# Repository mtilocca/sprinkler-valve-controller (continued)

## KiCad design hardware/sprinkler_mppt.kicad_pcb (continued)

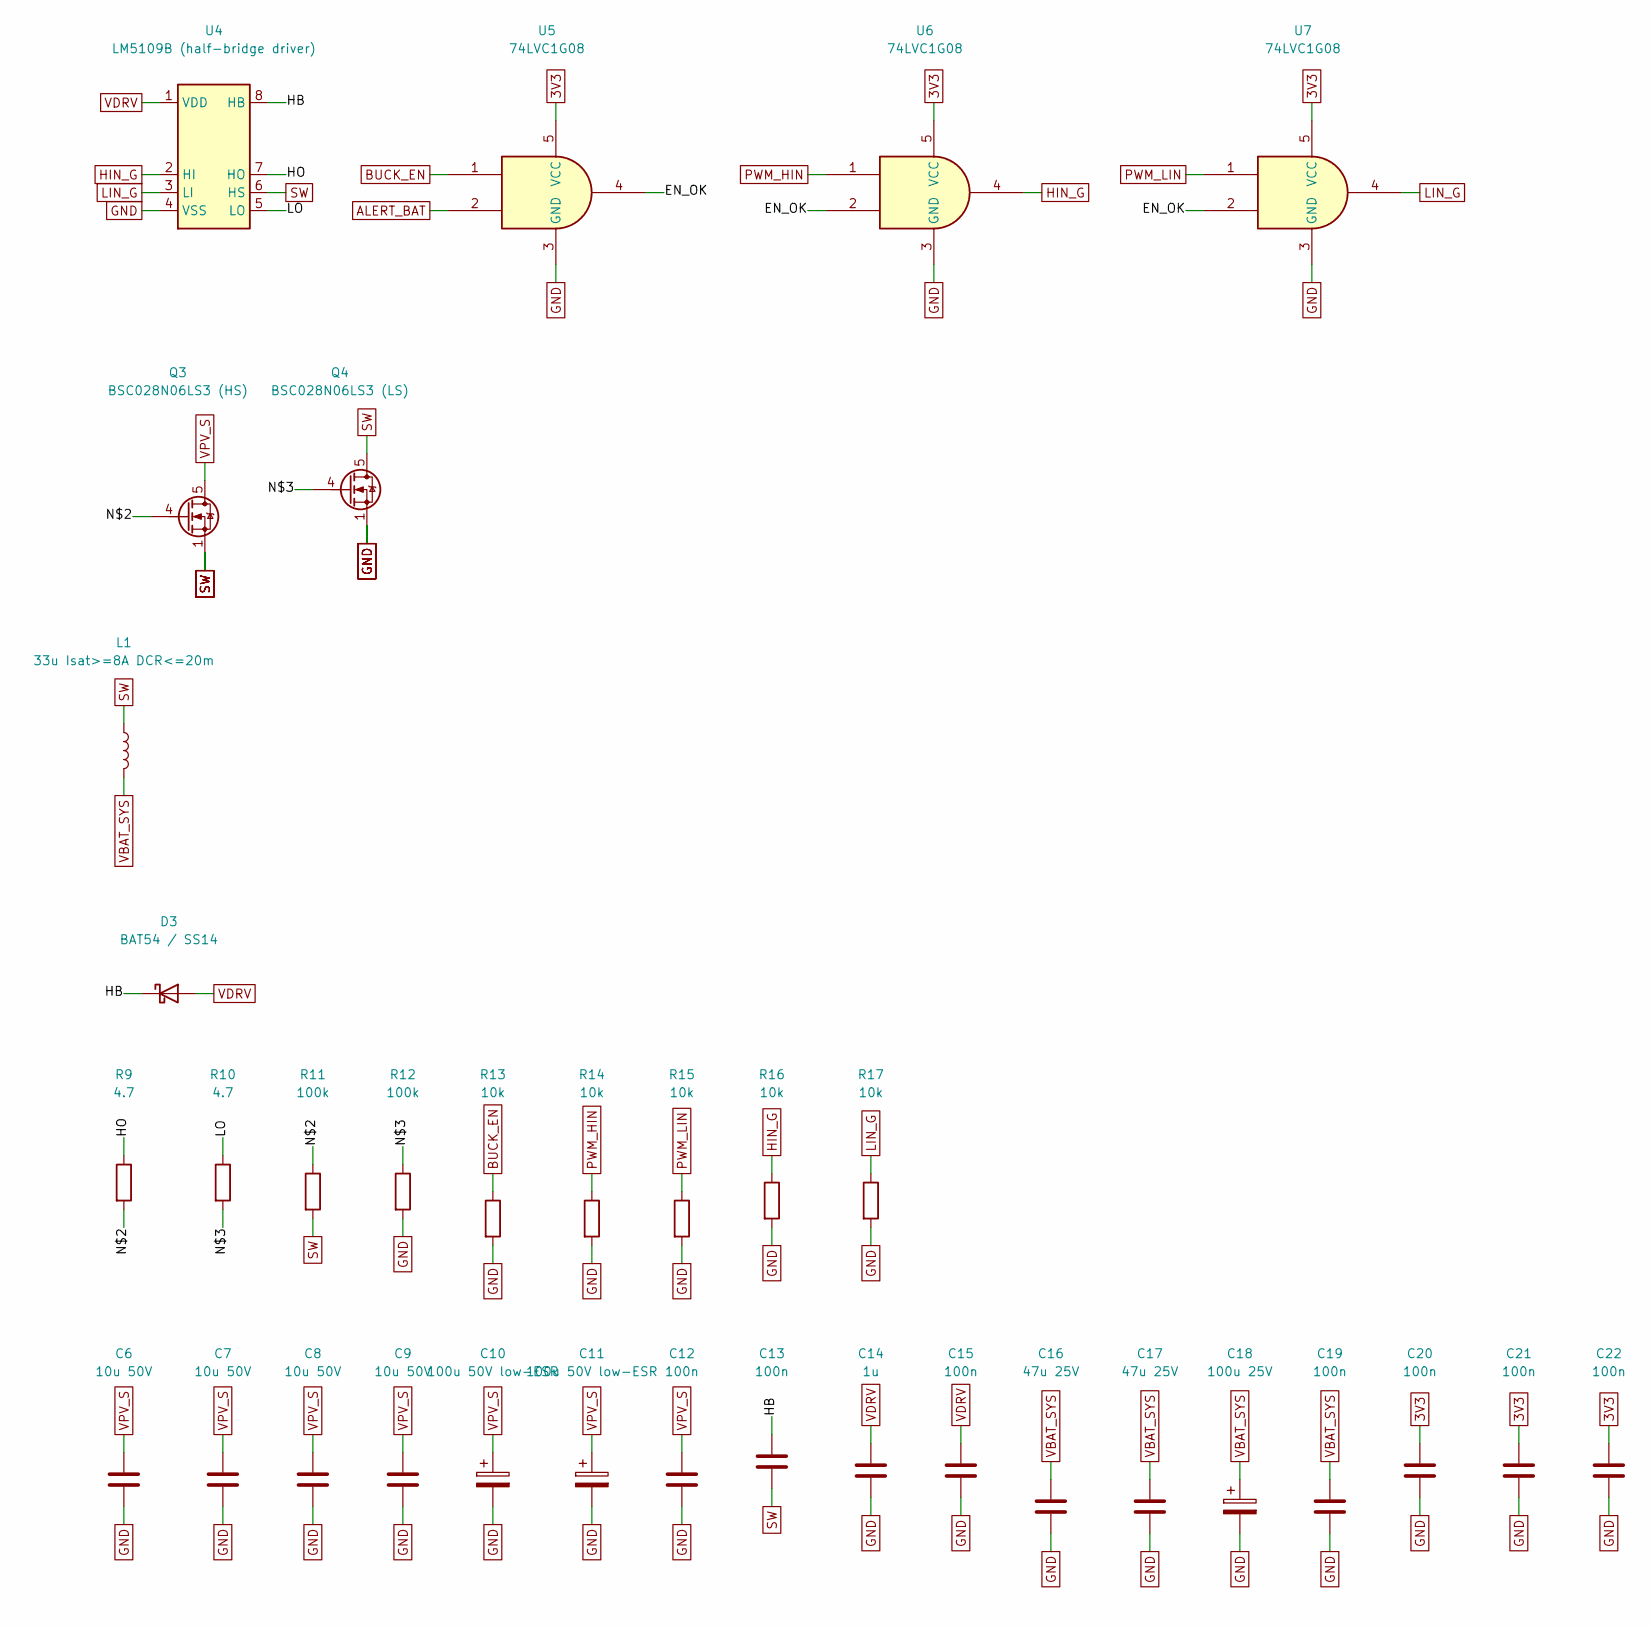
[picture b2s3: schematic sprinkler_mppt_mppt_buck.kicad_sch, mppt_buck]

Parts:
C6, C7, C8, C9: 10u 50V; C_1210_3225Metric
C10, C11: 100u 50V low-ESR; CP_Elec_8x10
C12, C13, C15, C19, C20, C21, C22: 100n; C_0603_1608Metric
C14: 1u; C_0603_1608Metric
C16, C17: 47u 25V; C_1210_3225Metric
C18: 100u 25V; CP_Elec_8x10
D3: BAT54 / SS14; D_SOD-123
L1: 33u Isat>=8A DCR<=20m; L_Bourns_SRP1245A
Q3: BSC028N06LS3 (HS); TDSON-8-1
Q4: BSC028N06LS3 (LS); TDSON-8-1
R9, R10: 4.7; R_0603_1608Metric
R11, R12: 100k; R_0603_1608Metric
R13, R14, R15, R16, R17: 10k; R_0603_1608Metric
U4: LM5109B (half-bridge driver); SOIC-8_3.9x4.9mm_P1.27mm
U5, U6, U7: 74LVC1G08; SOT-353_SC-70-5

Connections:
3V3: C20.1, C21.1, C22.1, U5.5 (VCC), U6.5 (VCC), U7.5 (VCC); also elsewhere on the board
/mppt_buck/EN_OK: U5.4, U6.2, U7.2
/mppt_buck/HB: C13.1, D3.1 (K), U4.8 (HB)
/mppt_buck/HO: R9.1, U4.7 (HO)
/mppt_buck/LO: R10.1, U4.5 (LO)
/mppt_buck/N$2: Q3.4 (G), R9.2, R11.1
/mppt_buck/N$3: Q4.4 (G), R10.2, R12.1
ALERT_BAT: U5.2; also elsewhere on the board
BUCK_EN: R13.1, U5.1; also elsewhere on the board
GND: C6.2, C7.2, C8.2, C9.2, C10.2, C11.2, C12.2, C14.2, C15.2, C16.2, C17.2, C18.2, C19.2, C20.2, C21.2, C22.2, Q4.1 (S), Q4.2 (S), Q4.3 (S), R12.2, R13.2, R14.2, R15.2, R16.2, R17.2, U4.4 (VSS), U5.3 (GND), U6.3 (GND), U7.3 (GND); also elsewhere on the board
HIN_G: R16.1, U4.2 (HI), U6.4; also elsewhere on the board
LIN_G: R17.1, U4.3 (LI), U7.4; also elsewhere on the board
PWM_HIN: R14.1, U6.1; also elsewhere on the board
PWM_LIN: R15.1, U7.1; also elsewhere on the board
SW: C13.2, L1.1, Q3.1 (S), Q3.2 (S), Q3.3 (S), Q4.5 (D), R11.2, U4.6 (HS); also elsewhere on the board
VBAT_SYS: C16.1, C17.1, C18.1, C19.1, L1.2; also elsewhere on the board
VDRV: C14.1, C15.1, D3.2 (A), U4.1 (VDD); also elsewhere on the board
VPV_S: C6.1, C7.1, C8.1, C9.1, C10.1, C11.1, C12.1, Q3.5 (D); also elsewhere on the board

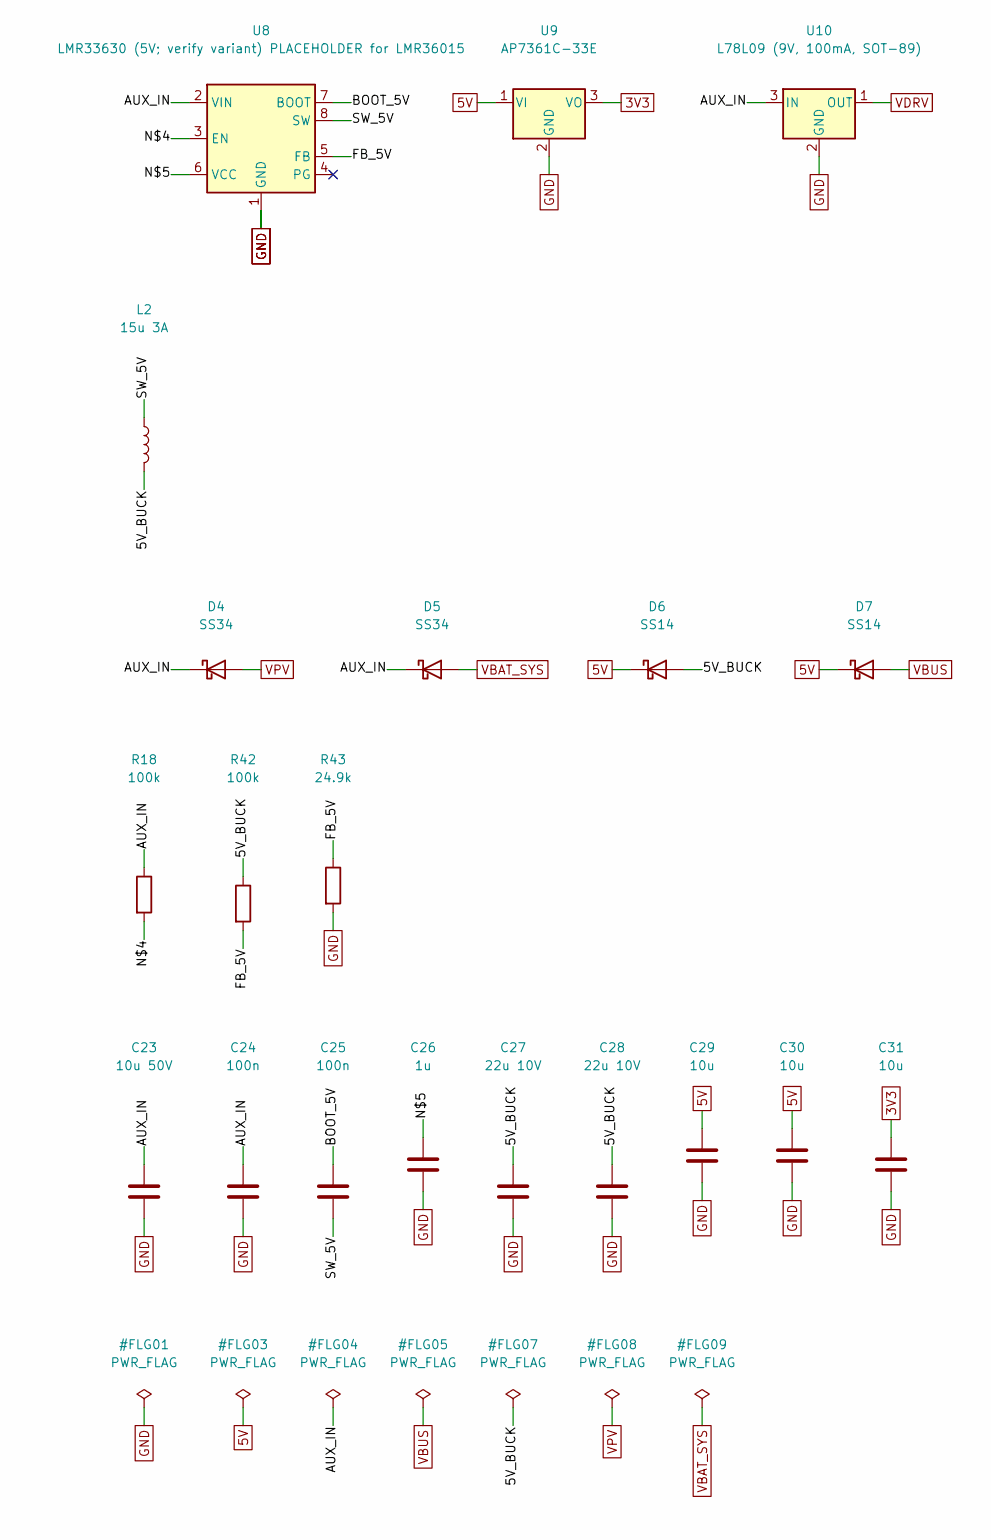
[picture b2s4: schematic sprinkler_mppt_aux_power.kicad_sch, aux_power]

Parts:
C23: 10u 50V; C_1210_3225Metric
C24, C25: 100n; C_0603_1608Metric
C26: 1u; C_0603_1608Metric
C27, C28: 22u 10V; C_1206_3216Metric
C29, C30, C31: 10u; C_1206_3216Metric
D4, D5: SS34; D_SMA
D6, D7: SS14; D_SMA
L2: 15u 3A; L_Bourns_SRN6045TA
R18: 100k; R_0603_1608Metric
R42: 100k; R_0402_1005Metric
R43: 24.9k; R_0402_1005Metric
U8: LMR33630 (5V; verify variant) PLACEHOLDER for LMR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; Texas_HSOP-8-1EP_3.9x4.9mm_P1.27mm_ThermalVias
U9: AP7361C-33E; SOT-223-3_TabPin2
U10: L78L09 (9V, 100mA, SOT-89); SOT-89-3

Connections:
3V3: C31.1, U9.3 (VO); also elsewhere on the board
5V: C29.1, C30.1, D6.1 (K), D7.1 (K), U9.1 (VI); also elsewhere on the board
/aux_power/5V_BUCK: C27.1, C28.1, D6.2 (A), L2.2, R42.1
/aux_power/AUX_IN: C23.1, C24.1, D4.1 (K), D5.1 (K), R18.1, U8.2 (VIN), U10.3 (IN)
/aux_power/BOOT_5V: C25.1, U8.7 (BOOT)
/aux_power/FB_5V: R42.2, R43.1, U8.5 (FB)
/aux_power/N$4: R18.2, U8.3 (EN)
/aux_power/N$5: C26.1, U8.6 (VCC)
/aux_power/SW_5V: C25.2, L2.1, U8.8 (SW)
GND: C23.2, C24.2, C26.2, C27.2, C28.2, C29.2, C30.2, C31.2, R43.2, U8.1 (GND), U8.9 (GND), U9.2 (GND), U10.2 (GND); also elsewhere on the board
VBAT_SYS: D5.2 (A); also elsewhere on the board
VBUS: D7.2 (A); also elsewhere on the board
VDRV: U10.1 (OUT); also elsewhere on the board
VPV: D4.2 (A); also elsewhere on the board

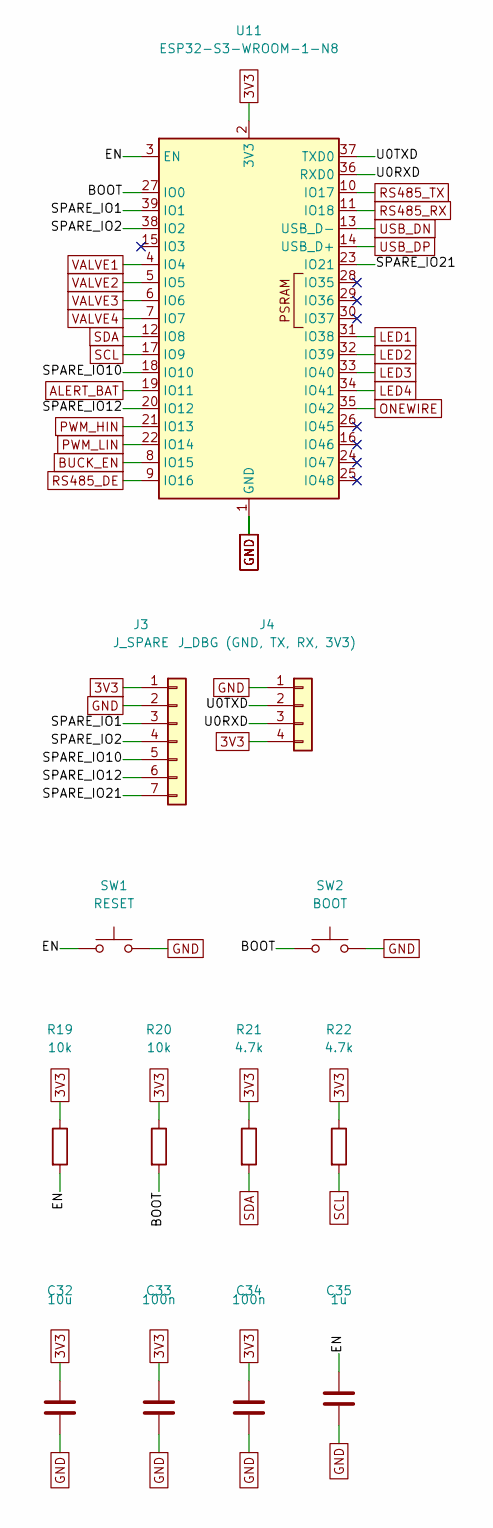
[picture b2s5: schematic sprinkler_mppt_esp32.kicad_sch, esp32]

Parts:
C32: 10u; C_1206_3216Metric
C33, C34: 100n; C_0603_1608Metric
C35: 1u; C_0603_1608Metric
J3: J_SPARE; PinHeader_1x07_P2.54mm_Vertical
J4: J_DBG (GND, TX, RX, 3V3); PinHeader_1x04_P2.54mm_Vertical
R19, R20: 10k; R_0603_1608Metric
R21, R22: 4.7k; R_0603_1608Metric
SW1: RESET; SW_SPST_PTS645Sx43SMTR92
SW2: BOOT; SW_SPST_PTS645Sx43SMTR92
U11: ESP32-S3-WROOM-1-N8; ESP32-S3-WROOM-1

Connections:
3V3: C32.1, C33.1, C34.1, J3.1, J4.4, R19.1, R20.1, R21.1, R22.1, U11.2 (3V3); also elsewhere on the board
/esp32/BOOT: R20.2, SW2.1, U11.27 (IO0)
/esp32/EN: C35.1, R19.2, SW1.1, U11.3 (EN)
/esp32/SPARE_IO1: J3.3, U11.39 (IO1)
/esp32/SPARE_IO2: J3.4, U11.38 (IO2)
/esp32/SPARE_IO10: J3.5, U11.18 (IO10)
/esp32/SPARE_IO12: J3.6, U11.20 (IO12)
/esp32/SPARE_IO21: J3.7, U11.23 (IO21)
/esp32/U0RXD: J4.3, U11.36 (RXD0)
/esp32/U0TXD: J4.2, U11.37 (TXD0)
ALERT_BAT: U11.19 (IO11); also elsewhere on the board
BUCK_EN: U11.8 (IO15); also elsewhere on the board
GND: C32.2, C33.2, C34.2, C35.2, J3.2, J4.1, SW1.2, SW2.2, U11.1 (GND), U11.40 (GND), U11.41 (GND); also elsewhere on the board
LED1: U11.31 (IO38); also elsewhere on the board
LED2: U11.32 (IO39); also elsewhere on the board
LED3: U11.33 (IO40); also elsewhere on the board
LED4: U11.34 (IO41); also elsewhere on the board
ONEWIRE: U11.35 (IO42); also elsewhere on the board
PWM_HIN: U11.21 (IO13); also elsewhere on the board
PWM_LIN: U11.22 (IO14); also elsewhere on the board
RS485_DE: U11.9 (IO16); also elsewhere on the board
RS485_RX: U11.11 (IO18); also elsewhere on the board
RS485_TX: U11.10 (IO17); also elsewhere on the board
SCL: R22.2, U11.17 (IO9); also elsewhere on the board
SDA: R21.2, U11.12 (IO8); also elsewhere on the board
USB_DN: U11.13 (USB_D-); also elsewhere on the board
USB_DP: U11.14 (USB_D+); also elsewhere on the board
VALVE1: U11.4 (IO4); also elsewhere on the board
VALVE2: U11.5 (IO5); also elsewhere on the board
VALVE3: U11.6 (IO6); also elsewhere on the board
VALVE4: U11.7 (IO7); also elsewhere on the board

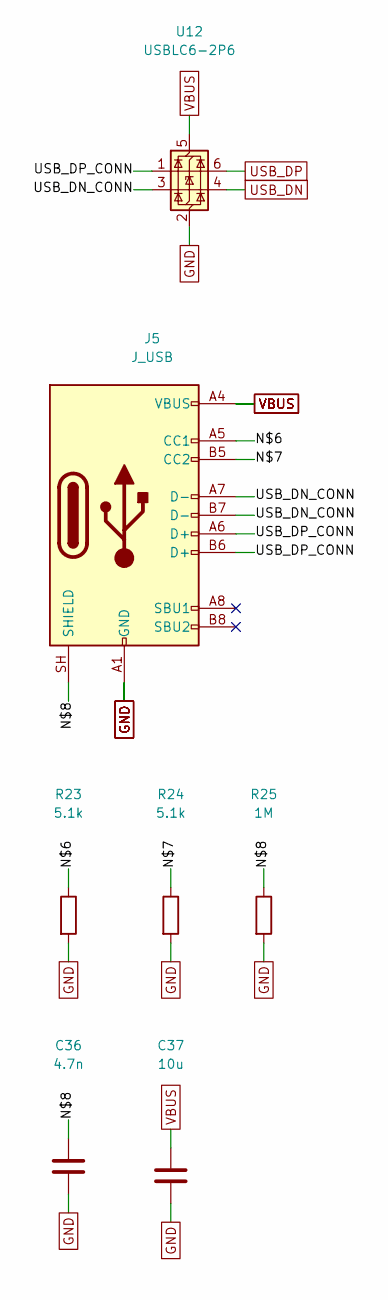
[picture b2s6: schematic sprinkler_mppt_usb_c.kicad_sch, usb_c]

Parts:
C36: 4.7n; C_0603_1608Metric
C37: 10u; C_1206_3216Metric
J5: J_USB; USB_C_Receptacle_HRO_TYPE-C-31-M-12
R23, R24: 5.1k; R_0603_1608Metric
R25: 1M; R_0603_1608Metric
U12: USBLC6-2P6; SOT-666

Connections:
/usb_c/N$6: J5.A5 (CC1), R23.1
/usb_c/N$7: J5.B5 (CC2), R24.1
/usb_c/N$8: C36.1, J5.SH (SHIELD), R25.1
/usb_c/USB_DN_CONN: J5.A7 (D-), J5.B7 (D-), U12.3 (I/O2)
/usb_c/USB_DP_CONN: J5.A6 (D+), J5.B6 (D+), U12.1 (I/O1)
GND: C36.2, C37.2, J5.A1 (GND), J5.A12 (GND), J5.B1 (GND), J5.B12 (GND), R23.2, R24.2, R25.2, U12.2 (GND); also elsewhere on the board
USB_DN: U12.4 (I/O2); also elsewhere on the board
USB_DP: U12.6 (I/O1); also elsewhere on the board
VBUS: C37.1, J5.A4 (VBUS), J5.A9 (VBUS), J5.B4 (VBUS), J5.B9 (VBUS), U12.5 (VBUS); also elsewhere on the board

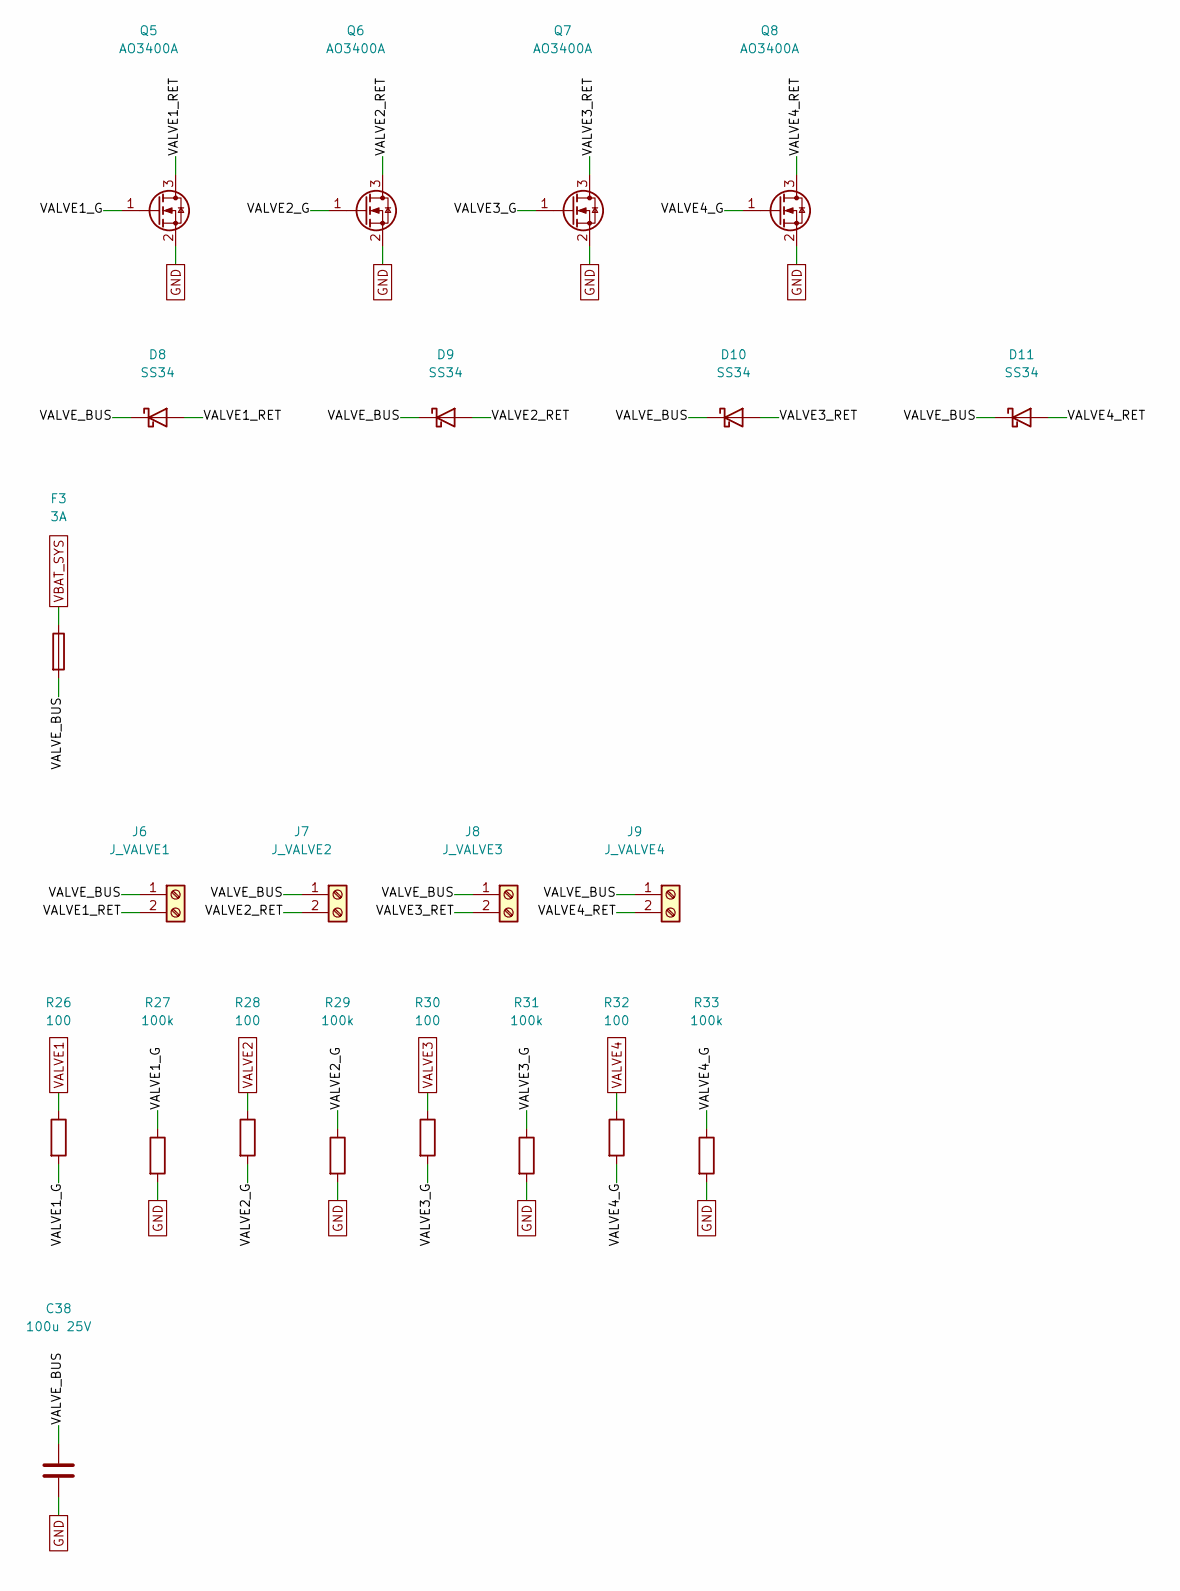
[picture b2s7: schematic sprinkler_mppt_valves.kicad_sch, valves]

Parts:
C38: 100u 25V; CP_Elec_8x10
D8, D9, D10, D11: SS34; D_SMA
F3: 3A; Fuse_1812_4532Metric
J6: J_VALVE1; TerminalBlock_Phoenix_MKDS-1,5-2-5.08_1x02_P5.08mm_Horizont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
J7: J_VALVE2; TerminalBlock_Phoenix_MKDS-1,5-2-5.08_1x02_P5.08mm_Horizont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
J8: J_VALVE3; TerminalBlock_Phoenix_MKDS-1,5-2-5.08_1x02_P5.08mm_Horizont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
J9: J_VALVE4; TerminalBlock_Phoenix_MKDS-1,5-2-5.08_1x02_P5.08mm_Horizont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
Q5, Q6, Q7, Q8: AO3400A; SOT-23
R26, R28, R30, R32: 100; R_0603_1608Metric
R27, R29, R31, R33: 100k; R_0603_1608Metric

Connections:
/valves/VALVE1_G: Q5.1 (G), R26.2, R27.1
/valves/VALVE1_RET: D8.2 (A), J6.2, Q5.3 (D)
/valves/VALVE2_G: Q6.1 (G), R28.2, R29.1
/valves/VALVE2_RET: D9.2 (A), J7.2, Q6.3 (D)
/valves/VALVE3_G: Q7.1 (G), R30.2, R31.1
/valves/VALVE3_RET: D10.2 (A), J8.2, Q7.3 (D)
/valves/VALVE4_G: Q8.1 (G), R32.2, R33.1
/valves/VALVE4_RET: D11.2 (A), J9.2, Q8.3 (D)
/valves/VALVE_BUS: C38.1, D8.1 (K), D9.1 (K), D10.1 (K), D11.1 (K), F3.2, J6.1, J7.1, J8.1, J9.1
GND: C38.2, Q5.2 (S), Q6.2 (S), Q7.2 (S), Q8.2 (S), R27.2, R29.2, R31.2, R33.2; also elsewhere on the board
VALVE1: R26.1; also elsewhere on the board
VALVE2: R28.1; also elsewhere on the board
VALVE3: R30.1; also elsewhere on the board
VALVE4: R32.1; also elsewhere on the board
VBAT_SYS: F3.1; also elsewhere on the board

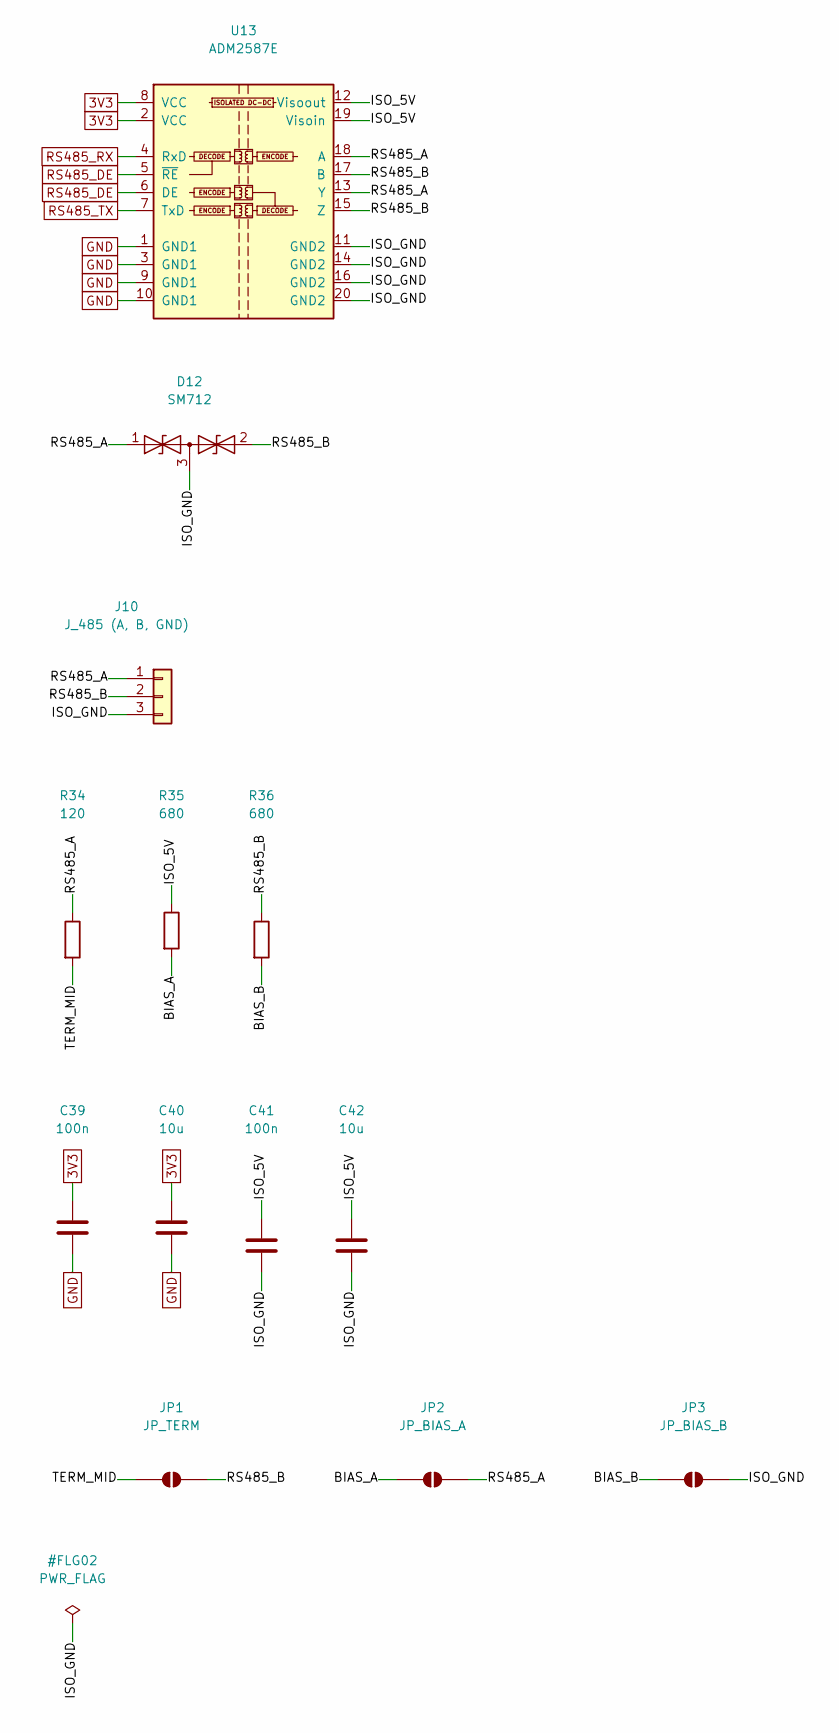
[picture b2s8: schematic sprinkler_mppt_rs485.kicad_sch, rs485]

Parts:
C39, C41: 100n; C_0603_1608Metric
C40, C42: 10u; C_1206_3216Metric
D12: SM712; SOT-23
J10: J_485 (A, B, GND); TerminalBlock_Phoenix_PT-1,5-3-3.5-H_1x03_P3.50mm_Horizontal
JP1: JP_TERM; SolderJumper-2_P1.3mm_Open_Pad1.0x1.5mm
JP2: JP_BIAS_A; SolderJumper-2_P1.3mm_Open_Pad1.0x1.5mm
JP3: JP_BIAS_B; SolderJumper-2_P1.3mm_Open_Pad1.0x1.5mm
R34: 120; R_0603_1608Metric
R35, R36: 680; R_0603_1608Metric
U13: ADM2587E; SOIC-20W_7.5x12.8mm_P1.27mm

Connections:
3V3: C39.1, C40.1, U13.2 (VCC), U13.8 (VCC); also elsewhere on the board
/rs485/BIAS_A: JP2.1 (A), R35.2
/rs485/BIAS_B: JP3.1 (A), R36.2
/rs485/ISO_5V: C41.1, C42.1, R35.1, U13.12 (Visoout), U13.19 (Visoin)
/rs485/ISO_GND: C41.2, C42.2, D12.3 (common), J10.3, JP3.2 (B), U13.11 (GND2), U13.14 (GND2), U13.16 (GND2), U13.20 (GND2)
/rs485/RS485_A: D12.1 (A1), J10.1, JP2.2 (B), R34.1, U13.13 (Y), U13.18 (A)
/rs485/RS485_B: D12.2 (A2), J10.2, JP1.2 (B), R36.1, U13.15 (Z), U13.17 (B)
/rs485/TERM_MID: JP1.1 (A), R34.2
GND: C39.2, C40.2, U13.1 (GND1), U13.3 (GND1), U13.9 (GND1), U13.10 (GND1); also elsewhere on the board
RS485_DE: U13.5 (~RE), U13.6 (DE); also elsewhere on the board
RS485_RX: U13.4 (RxD); also elsewhere on the board
RS485_TX: U13.7 (TxD); also elsewhere on the board

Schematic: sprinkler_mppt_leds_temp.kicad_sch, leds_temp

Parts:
D13: green; LED_0603_1608Metric
D14: yellow; LED_0603_1608Metric
D15: blue; LED_0603_1608Metric
D16: red; LED_0603_1608Metric
J11: J_TEMP (3V3, DQ, GND) DS18B20; JST_XH_B3B-XH-A_1x03_P2.50mm_Vertical
R37, R38: 620; R_0603_1608Metric
R39: 200; R_0603_1608Metric
R40: 680; R_0603_1608Metric
R41: 4.7k; R_0603_1608Metric

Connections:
3V3: J11.1, R41.1; also elsewhere on the board
/leds_temp/LED1_A: D13.2 (A), R37.2
/leds_temp/LED2_A: D14.2 (A), R38.2
/leds_temp/LED3_A: D15.2 (A), R39.2
/leds_temp/LED4_A: D16.2 (A), R40.2
GND: D13.1 (K), D14.1 (K), D15.1 (K), D16.1 (K), J11.3; also elsewhere on the board
LED1: R37.1; also elsewhere on the board
LED2: R38.1; also elsewhere on the board
LED3: R39.1; also elsewhere on the board
LED4: R40.1; also elsewhere on the board
ONEWIRE: J11.2, R41.2; also elsewhere on the board

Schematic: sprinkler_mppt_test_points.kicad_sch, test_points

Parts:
TP1, TP2, TP3, TP4, TP5, TP6, TP7, TP8, TP9, TP10, TP11: TP; TestPoint_Pad_D1.5mm

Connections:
3V3: TP4.1; also elsewhere on the board
5V: TP3.1; also elsewhere on the board
ALERT_BAT: TP11.1; also elsewhere on the board
GND: TP7.1, TP8.1; also elsewhere on the board
HIN_G: TP9.1; also elsewhere on the board
LIN_G: TP10.1; also elsewhere on the board
SW: TP6.1; also elsewhere on the board
VBAT_SYS: TP2.1; also elsewhere on the board
VDRV: TP5.1; also elsewhere on the board
VPV_S: TP1.1; also elsewhere on the board

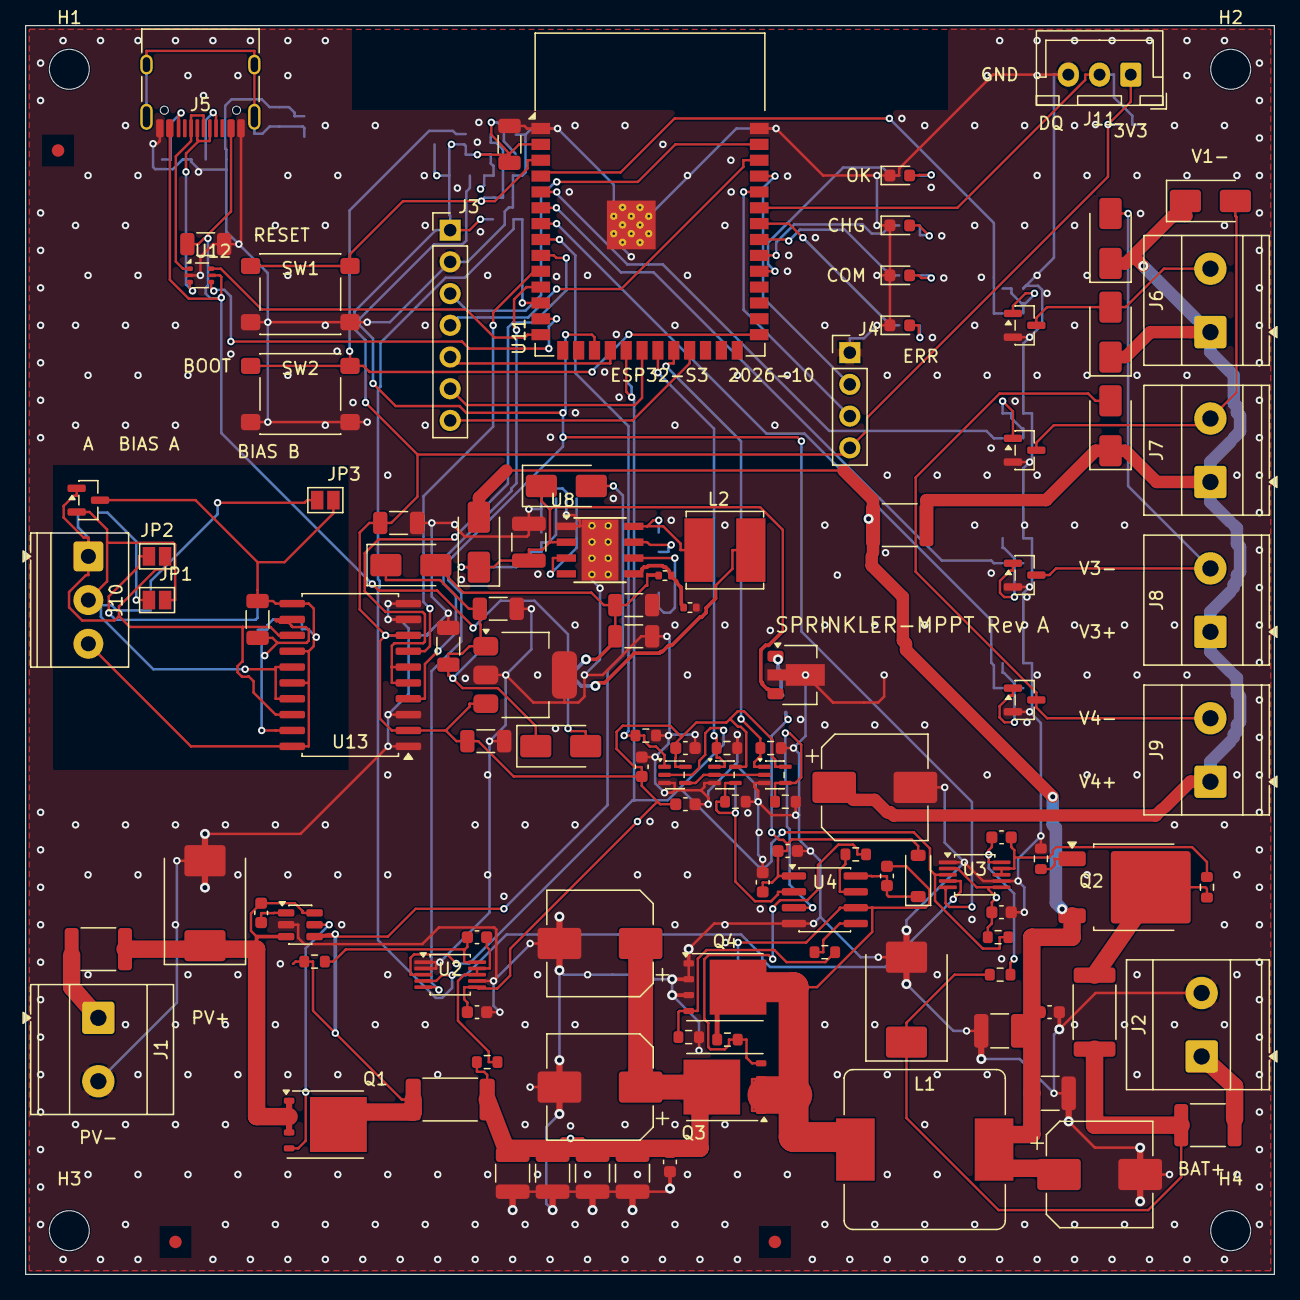
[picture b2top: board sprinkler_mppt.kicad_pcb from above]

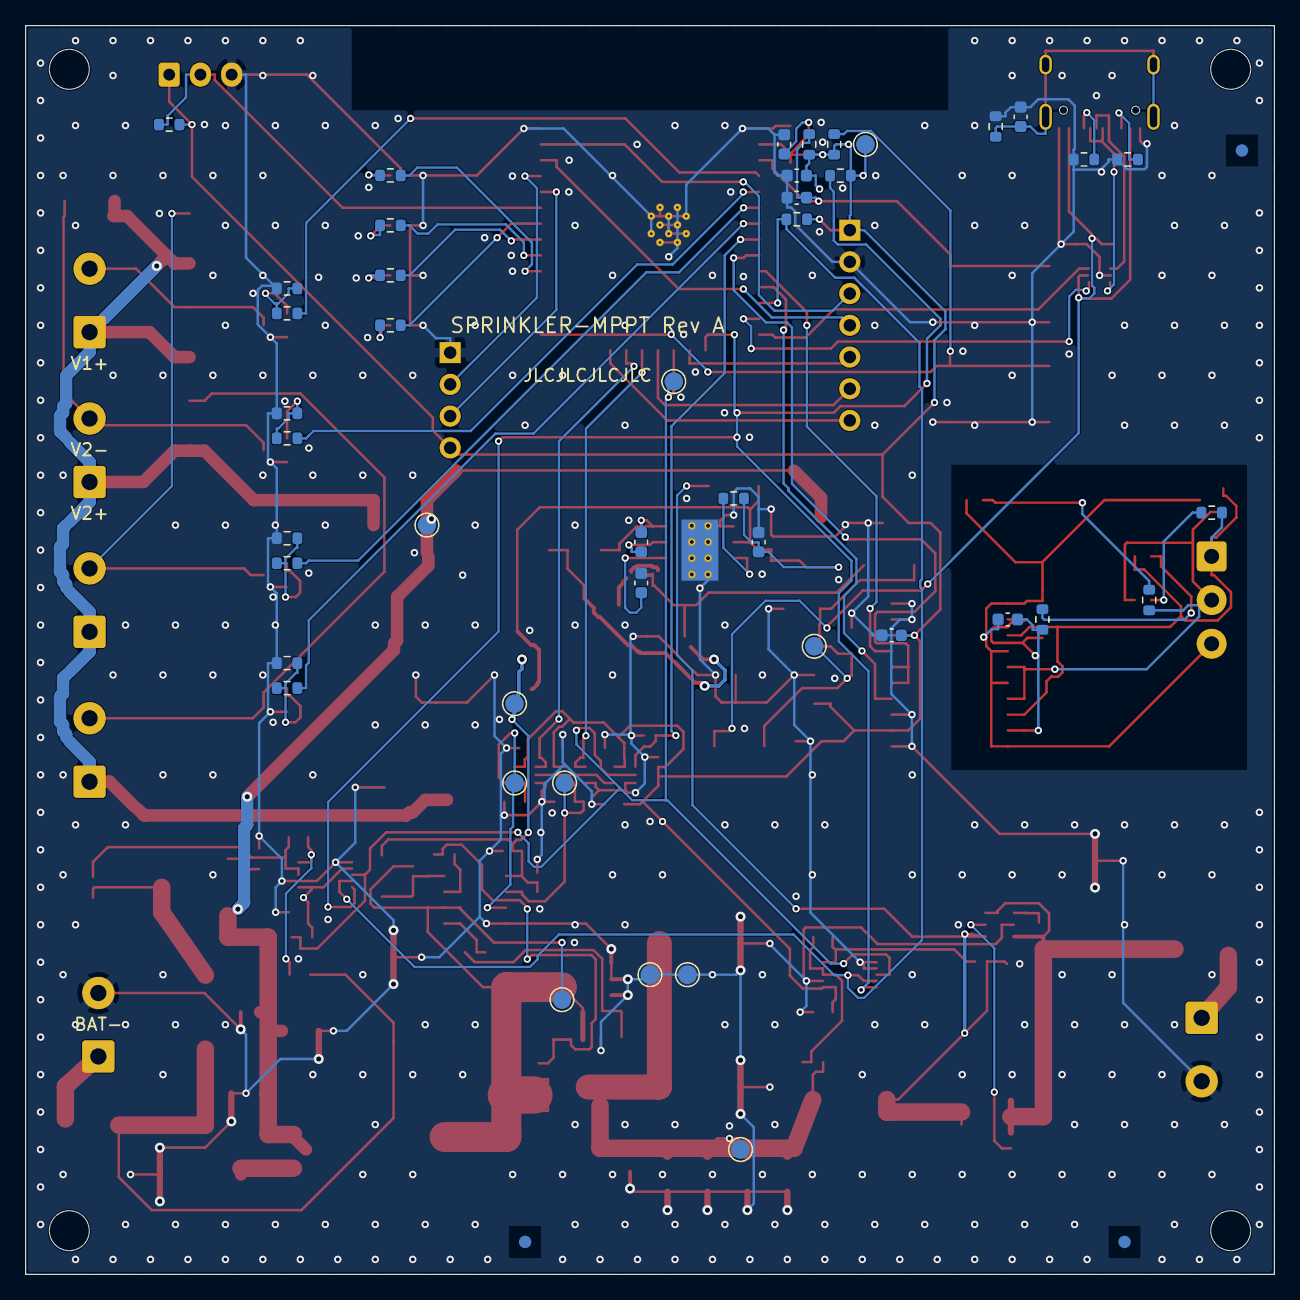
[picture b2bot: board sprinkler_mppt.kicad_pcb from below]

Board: 4 copper layers, 100.0 x 100.0 mm, 164 parts (47 on the bottom side), 90 nets.

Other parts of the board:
FID1B, FID1T, FID2B, FID2T, FID3B, FID3T: Fiducial; Fiducial_1mm_Mask2mm
H1, H2, H3, H4: M3; MountingHole_3.2mm_M3

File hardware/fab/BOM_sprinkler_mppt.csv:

Designators,Qty,Value,Footprint,Suggested part (VERIFY against datasheet),LCSC part # (to fill),Est. unit USD (rough),Est. line USD (rough)
"C1-C5,C12,C13,C15,C19-C22,C24,C25,C33,C34,C39,C41",18,100n,C_0603_1608Metric,Samsung CL10B104KB8NNNC (X7R 50V),,0.004,0.07
"C6-C9,C23",5,10u 50V,C_1210_3225Metric,Samsung CL32B106KBJNNNE (X7R 50V),,0.350,1.75
"C10,C11",2,100u 50V low-ESR,CP_Elec_8x10,"Panasonic EEEFK1H101P or equivalent, 8x10.2 SMD, 50V",,0.450,0.90
"C14,C26,C35",3,1u,C_0603_1608Metric,Samsung CL10A105KA8NNNC (25V),,0.010,0.03
"C16,C17",2,47u 25V,C_1210_3225Metric,Samsung CL32A476MAJNNNE (X5R 25V),,0.450,0.90
"C18,C38",2,100u 25V,CP_Elec_8x10,"Panasonic EEEFK1E101P or equivalent, 8x10.2 SMD, 25V",,0.300,0.60
"C27,C28",2,22u 10V,C_1206_3216Metric,Samsung CL31A226MPHNNNE (X5R 10V) - consider 4x per datasheet,,0.150,0.30
"C29-C32,C37,C40,C42",7,10u,C_1206_3216Metric,Samsung CL31B106KAHNNNE (X7R 25V),,0.120,0.84
C36,1,4.7n,C_0603_1608Metric,Samsung CL10B472KB8NNNC,,0.005,0.01
D1,1,SMDJ26A,D_SMC,Littelfuse SMDJ26A,,0.350,0.35
D2,1,SMDJ16A,D_SMC,Littelfuse SMDJ16A,,0.350,0.35
D3,1,BAT54 / SS14,D_SOD-123,"BAT54 Schottky SOD-123 (e.g. onsemi BAT54HT1G) - value text says BAT54 / SS14, pick one",,0.040,0.04
"D4,D5,D8-D11",6,SS34,D_SMA,"SS34 (3A 40V Schottky, SMA)",,0.060,0.36
"D6,D7",2,SS14,D_SMA,"SS14 (1A 40V Schottky, SMA)",,0.040,0.08
D12,1,SM712,SOT-23,Semtech SM712.TCT,,0.300,0.30
D13,1,green,LED_0603_1608Metric,"generic 0603 LED, green",,0.030,0.03
D14,1,yellow,LED_0603_1608Metric,"generic 0603 LED, yellow",,0.030,0.03
D15,1,blue,LED_0603_1608Metric,"generic 0603 LED, blue",,0.040,0.04
D16,1,red,LED_0603_1608Metric,"generic 0603 LED, red",,0.030,0.03
F1,1,5A,Fuse_1812_4532Metric,"1812 SMD fuse 5A >=32VDC (VERIFY part exists, e.g. Littelfuse NANO2 series)",,0.400,0.40
F2,1,10A,Fuse_1812_4532Metric,1812 SMD fuse 10A >=32VDC (VERIFY: 10A in 1812 is rare; may need a different package),,0.800,0.80
F3,1,3A,Fuse_1812_4532Metric,1812 SMD fuse 3A >=32VDC,,0.350,0.35
J1,1,J_PV panel,TerminalBlock_Phoenix_MKDS-3-2-5.08_1x02_P5.08mm_Horizontal,"Phoenix MKDS 1,5/ 2-5.08 or equivalent 5.08mm 2-pin (e.g. KF128-5.08-2P)",,0.450,0.45
J2,1,J_BAT battery,TerminalBlock_Phoenix_MKDS-3-2-5.08_1x02_P5.08mm_Horizontal,"Phoenix MKDS 1,5/ 2-5.08 or equivalent 5.08mm 2-pin",,0.450,0.45
J3,1,J_SPARE,PinHeader_1x07_P2.54mm_Vertical,1x7 pin header 2.54mm,,0.100,0.10
J4,1,"J_DBG (GND, TX, RX, 3V3)",PinHeader_1x04_P2.54mm_Vertical,1x4 pin header 2.54mm,,0.060,0.06
J5,1,J_USB,USB_C_Receptacle_HRO_TYPE-C-31-M-12,HRO TYPE-C-31-M-12 (USB-C 16-pin receptacle),,0.300,0.30
J6,1,J_VALVE1,"TerminalBlock_Phoenix_MKDS-1,5-2-5.08_1x02_P5.08mm_Horizontal","Phoenix MKDS 1,5/ 2-5.08 or equivalent 5.08mm 2-pin (e.g. KF128-5.08-2P)",,0.450,0.45
J7,1,J_VALVE2,"TerminalBlock_Phoenix_MKDS-1,5-2-5.08_1x02_P5.08mm_Horizontal","Phoenix MKDS 1,5/ 2-5.08 or equivalent 5.08mm 2-pin (e.g. KF128-5.08-2P)",,0.450,0.45
J8,1,J_VALVE3,"TerminalBlock_Phoenix_MKDS-1,5-2-5.08_1x02_P5.08mm_Horizontal","Phoenix MKDS 1,5/ 2-5.08 or equivalent 5.08mm 2-pin (e.g. KF128-5.08-2P)",,0.450,0.45
J9,1,J_VALVE4,"TerminalBlock_Phoenix_MKDS-1,5-2-5.08_1x02_P5.08mm_Horizontal","Phoenix MKDS 1,5/ 2-5.08 or equivalent 5.08mm 2-pin (e.g. KF128-5.08-2P)",,0.450,0.45
J10,1,"J_485 (A, B, GND)","TerminalBlock_Phoenix_PT-1,5-3-3.5-H_1x03_P3.50mm_Horizontal","Phoenix PT 1,5/3-3.5-H or equivalent 3.5mm 3-pin",,0.400,0.40
J11,1,"J_TEMP (3V3, DQ, GND) DS18B20",JST_XH_B3B-XH-A_1x03_P2.50mm_Vertical,JST B3B-XH-A,,0.120,0.12
JP1,1,JP_TERM,SolderJumper-2_P1.3mm_Open_Pad1.0x1.5mm,"solder jumper (copper pads, no part)",,0.000,0.00
JP2,1,JP_BIAS_A,SolderJumper-2_P1.3mm_Open_Pad1.0x1.5mm,"solder jumper (copper pads, no part)",,0.000,0.00
JP3,1,JP_BIAS_B,SolderJumper-2_P1.3mm_Open_Pad1.0x1.5mm,"solder jumper (copper pads, no part)",,0.000,0.00
L1,1,33u Isat>=8A DCR<=20m,L_Bourns_SRP1245A,Bourns SRP1245A-330M (verify Isat),,2.200,2.20
L2,1,15u 3A,L_Bourns_SRN6045TA,Bourns SRN6045TA-150M (verify Isat >= 3A; datasheet suggests 8 uH),,0.500,0.50
Q1,1,BSC028N06LS3,TDSON-8-1,Infineon BSC028N06LS3 G,,1.100,1.10
Q2,1,SUD45P03-09,TO-252-2,Vishay SUD45P03-09-GE3,,0.900,0.90
Q3,1,BSC028N06LS3 (HS),TDSON-8-1,Infineon BSC028N06LS3 G,,1.100,1.10
Q4,1,BSC028N06LS3 (LS),TDSON-8-1,Infineon BSC028N06LS3 G,,1.100,1.10
Q5-Q8,4,AO3400A,SOT-23,Alpha&Omega AO3400A,,0.040,0.16
"R1,R4",2,5m 1W Kelvin,R_2512_6332Metric,"5 mOhm 1W 2512, 1% (e.g. Yageo PA2512FKF7W0R005E - verify)",,0.350,0.70
"R2,R3,R5,R6",4,10,R_0603_1608Metric,"generic thick-film resistor 1%, 0603",,0.003,0.01
"R7,R8,R13-R17,R19,R20",9,10k,R_0603_1608Metric,"generic thick-film resistor 1%, 0603",,0.003,0.03
"R9,R10",2,4.7,R_0603_1608Metric,"generic thick-film resistor 1%, 0603",,0.003,0.01
"R11,R12,R18,R27,R29,R31,R33",7,100k,R_0603_1608Metric,"generic thick-film resistor 1%, 0603",,0.003,0.02
"R21,R22,R41",3,4.7k,R_0603_1608Metric,"generic thick-film resistor 1%, 0603",,0.003,0.01
"R23,R24",2,5.1k,R_0603_1608Metric,"generic thick-film resistor 1%, 0603",,0.003,0.01
R25,1,1M,R_0603_1608Metric,"generic thick-film resistor 1%, 0603",,0.003,0.00
"R26,R28,R30,R32",4,100,R_0603_1608Metric,"generic thick-film resistor 1%, 0603",,0.003,0.01
R34,1,120,R_0603_1608Metric,"generic thick-film resistor 1%, 0603",,0.003,0.00
"R35,R36,R40",3,680,R_0603_1608Metric,"generic thick-film resistor 1%, 0603",,0.003,0.01
"R37,R38",2,620,R_0603_1608Metric,"generic thick-film resistor 1%, 0603",,0.003,0.01
R39,1,200,R_0603_1608Metric,"generic thick-film resistor 1%, 0603",,0.003,0.00
R42,1,100k,R_0402_1005Metric,"generic thick-film resistor 1%, 0402",,0.003,0.00
R43,1,24.9k,R_0402_1005Metric,"generic thick-film resistor 1%, 0402",,0.003,0.00
SW1,1,RESET,SW_SPST_PTS645Sx43SMTR92,C&K PTS645SK43SMTR92 LFS tactile switch,,0.120,0.12
SW2,1,BOOT,SW_SPST_PTS645Sx43SMTR92,C&K PTS645SK43SMTR92 LFS tactile switch,,0.120,0.12
TP1-TP11,11,TP,TestPoint_Pad_D1.5mm,"test pad (copper only, no part)",,0.000,0.00
U1,1,LM74700-Q1,SOT-23-6,TI LM74700QDBVRQ1,,1.300,1.30
U2,1,"INA228 (PV, 0x40)",TSSOP-10_3x3mm_P0.5mm,TI INA228AIDGSR,,4.200,4.20
U3,1,"INA228 (BAT, 0x41)",TSSOP-10_3x3mm_P0.5mm,TI INA228AIDGSR,,4.200,4.20
U4,1,LM5109B (half-bridge driver),SOIC-8_3.9x4.9mm_P1.27mm,TI LM5109BMAX/NOPB,,1.200,1.20
U5-U7,3,74LVC1G08,SOT-353_SC-70-5,TI SN74LVC1G08DCKR,,0.100,0.30
U8,1,LMR33630 (5V; verify variant) PLACEHOLDER for LMR36015,Texas_HSOP-8-1EP_3.9x4.9mm_P1.27mm_ThermalVias,"TI LMR33630ADDAR (adjustable, uses R42/R43)",,2.200,2.20
U9,1,AP7361C-33E,SOT-223-3_TabPin2,Diodes AP7361C-33E-13,,0.450,0.45
U10,1,"L78L09 (9V, 100mA, SOT-89)",SOT-89-3,ST L78L09ABUTR,,0.200,0.20
U11,1,ESP32-S3-WROOM-1-N8,ESP32-S3-WROOM-1,Espressif ESP32-S3-WROOM-1-N8,,4.200,4.20
U12,1,USBLC6-2P6,SOT-666,ST USBLC6-2P6,,0.300,0.30
U13,1,ADM2587E,SOIC-20W_7.5x12.8mm_P1.27mm,Analog Devices ADM2587EBRWZ,,10.000,10.00

,,,,"TOTAL parts per board (rough estimate, not a quote)",,,48.91
